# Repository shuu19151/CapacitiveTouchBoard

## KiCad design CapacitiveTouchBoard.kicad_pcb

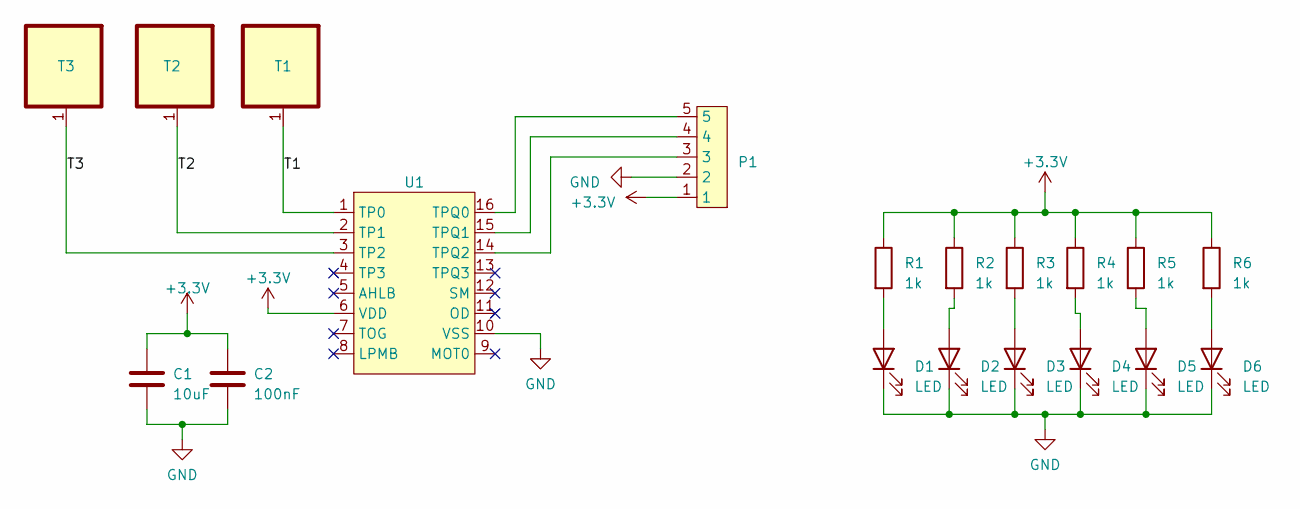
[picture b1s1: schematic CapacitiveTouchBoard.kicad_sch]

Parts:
C1: 10uF; C_0603
C2: 100nF; C_0603
D1, D2, D3, D4, D5, D6: LED; LED_0805_ReverseMount_Hole1.8x2mm
P1: JST_SH_SM05B-SRSS-TB_1x05-1MP_P1.00mm_Horizontal
R1, R2, R3, R4, R5, R6: 1k; R_0603
T1, T2, T3: TouchPad_12x12mm
U1: SSOP-16

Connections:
+3.3V: C1.1, C2.1, P1.1, R1.1, R2.1, R3.1, R4.1, R5.1, R6.1, U1.6 (VDD)
/T1: T1.1, U1.1 (TP0)
/T2: T2.1, U1.2 (TP1)
/T3: T3.1, U1.3 (TP2)
GND: C1.2, C2.2, D1.1 (K), D2.1 (K), D3.1 (K), D4.1 (K), D5.1 (K), D6.1 (K), P1.2, U1.10 (VSS)
unnamed: D1.2 (A), R1.2
unnamed: D2.2 (A), R2.2
unnamed: D3.2 (A), R3.2
unnamed: D4.2 (A), R4.2
unnamed: D5.2 (A), R5.2
unnamed: D6.2 (A), R6.2
unnamed: P1.5, U1.16 (TPQ0)
unnamed: P1.4, U1.15 (TPQ1)
unnamed: P1.3, U1.14 (TPQ2)

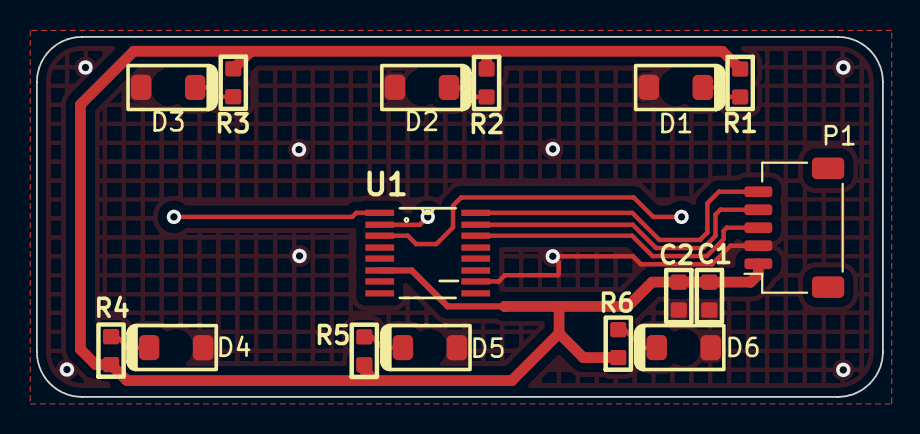
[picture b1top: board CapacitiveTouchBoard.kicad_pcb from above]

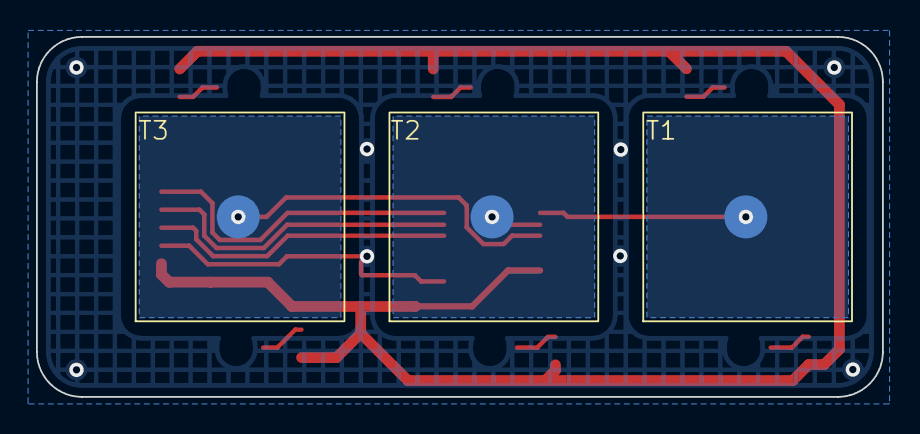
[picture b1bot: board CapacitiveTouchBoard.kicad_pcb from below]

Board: 2 copper layers, 47.0 x 20.0 mm, 19 parts (3 on the bottom side), 14 nets.
